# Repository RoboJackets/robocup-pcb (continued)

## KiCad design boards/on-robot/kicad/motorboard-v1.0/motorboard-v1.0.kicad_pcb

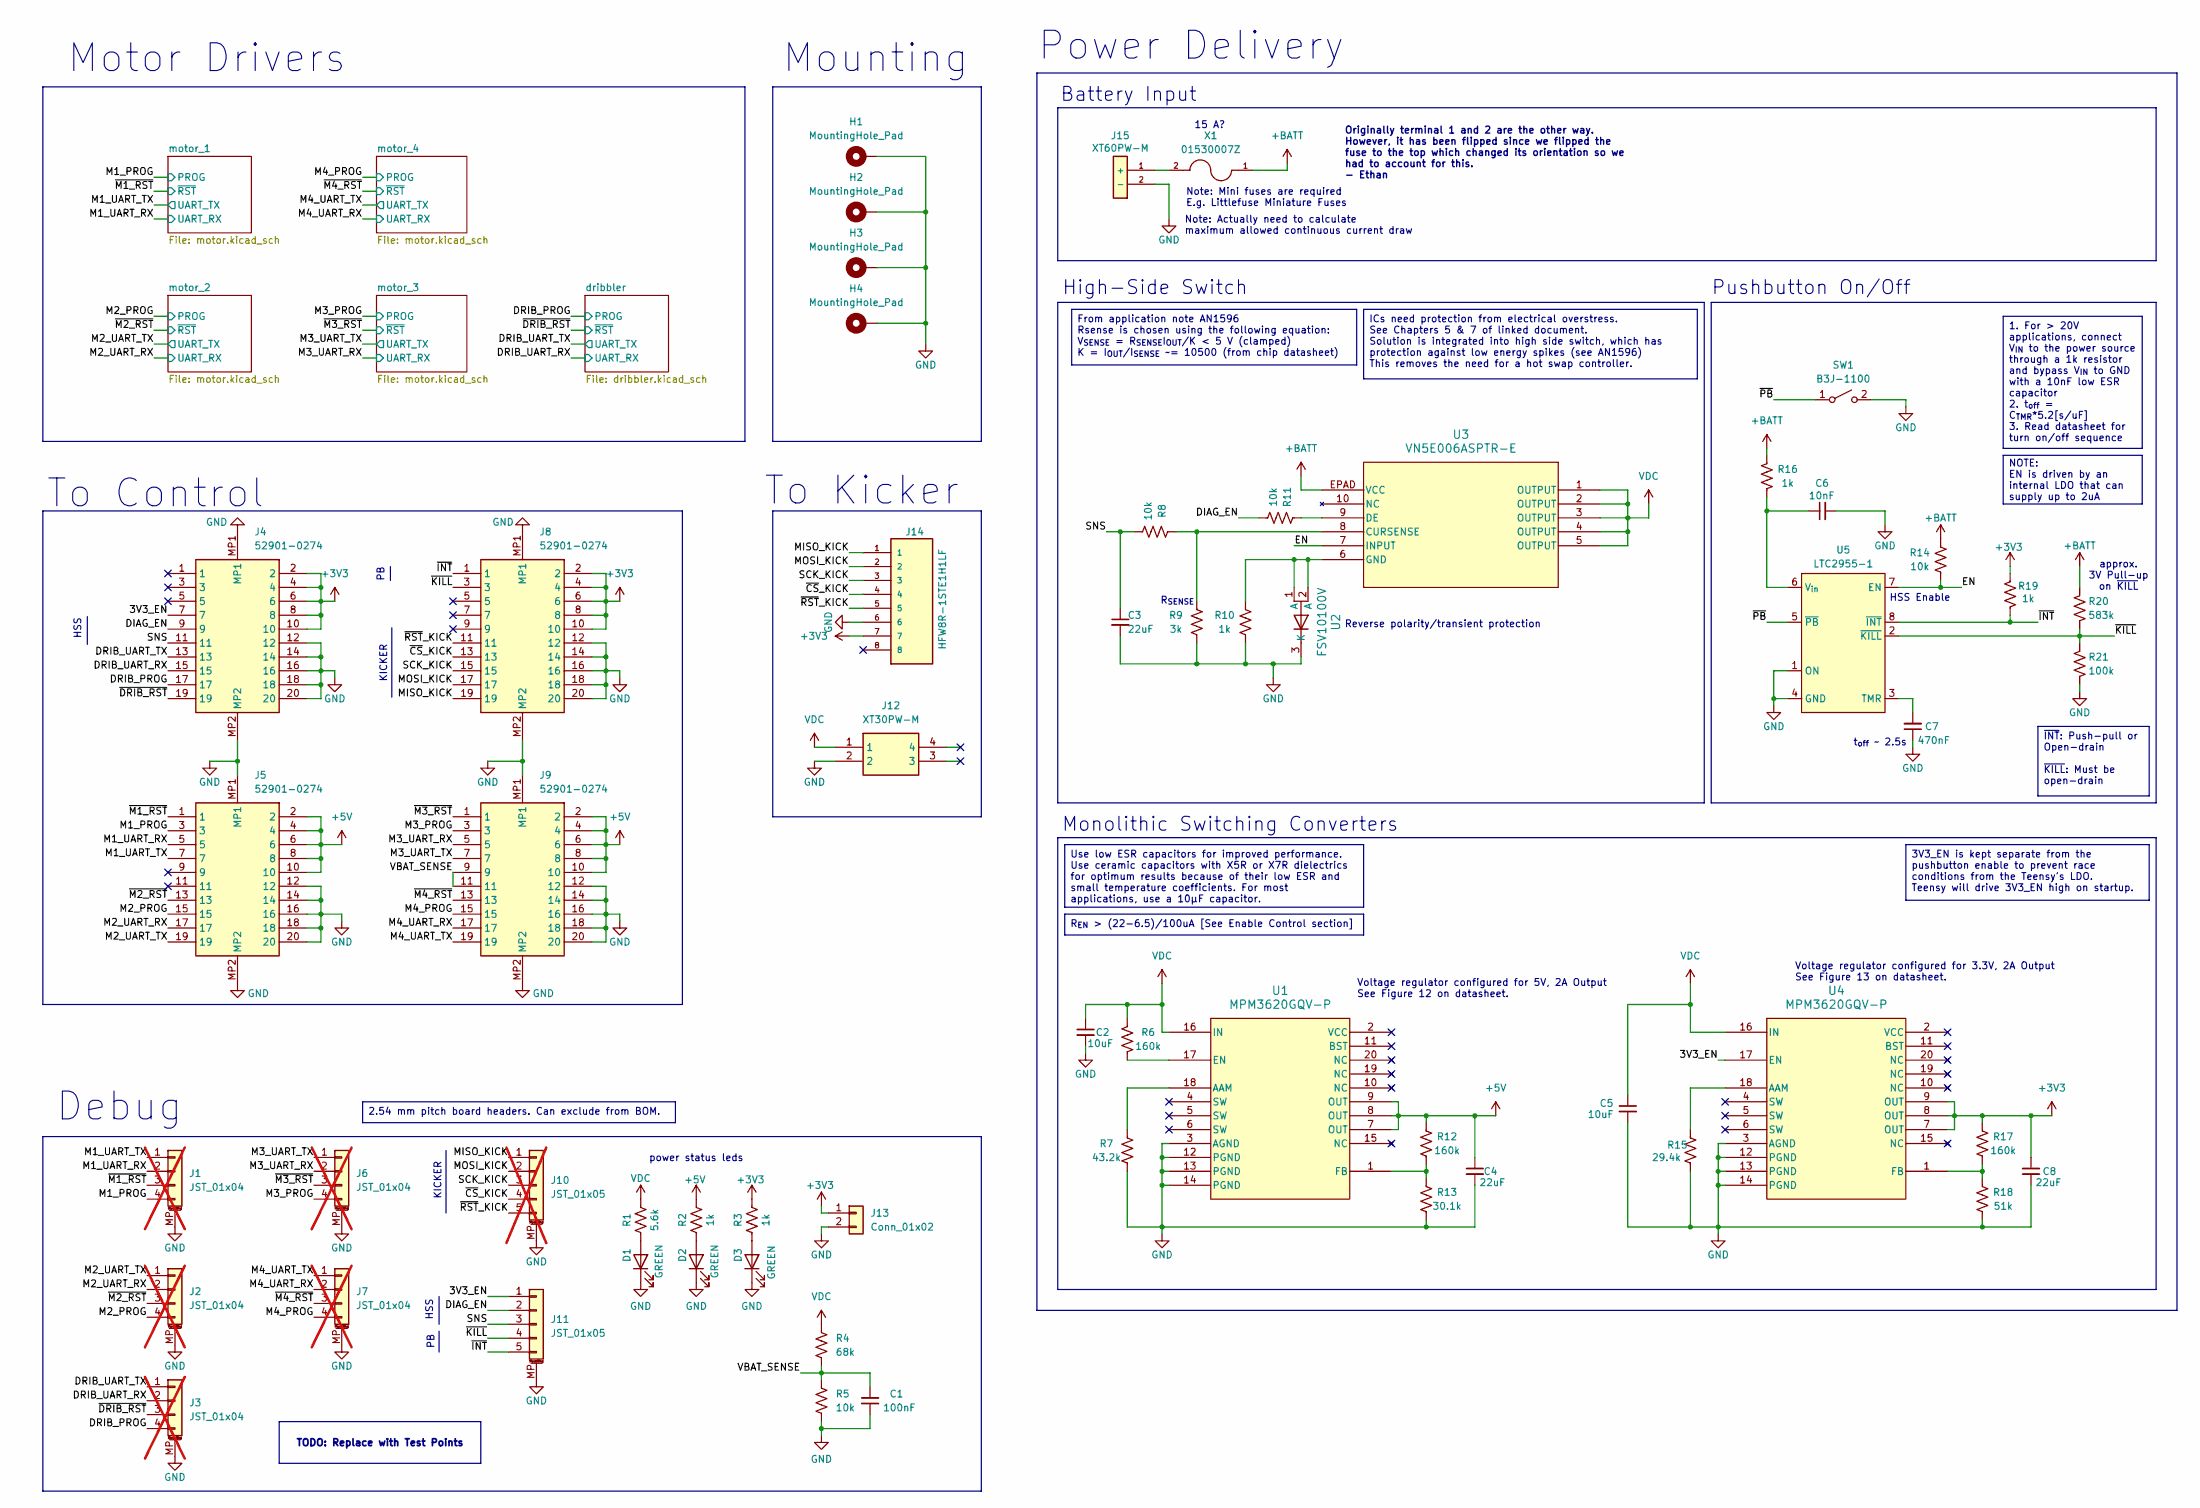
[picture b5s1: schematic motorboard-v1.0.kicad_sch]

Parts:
C1: 100nF; C_0603_1608Metric
C2, C5: 10uF; C_1206_3216Metric
C3, C4, C8: 22uF; C_1206_3216Metric
C6: 10nF; C_0603_1608Metric
C7: 470nF; C_0603_1608Metric
D1, D2, D3: GREEN; D_0603_1608Metric
H1, H2, H3, H4: MountingHole_Pad; MountingHole_3.7mm_Pad
J1, J2, J3, J6, J7: JST_01x04; JST_SH_BM04B-SRSS-TB_1x04-1MP_P1.00mm_Vertical; not fitted
J4, J5, J8, J9: 52901-0274; 529010274; Manufacturer_Part_Number 52901-0274; Mouser Part Number 538-52901-0274
J10: JST_01x05; JST_SH_BM05B-SRSS-TB_1x05-1MP_P1.00mm_Vertical; not fitted
J11: JST_01x05; JST_SH_BM05B-SRSS-TB_1x05-1MP_P1.00mm_Vertical
J12: XT30PW-M; XT30PWM; Manufacturer P/N XT30PW-M
J13: Conn_01x02; PinHeader_1x02_P2.54mm_Vertical
J14: HFW8R-1STE1H1LF; AMPHENOL_HFW8R-1STE1H1LF; PARTREV B
J15: XT60PW-M; XT60PWM; Manufacturer P/N XT60PW-M
R1: 5.6k; R_0603_1608Metric
R2, R3, R10, R16, R19: 1k; R_0603_1608Metric
R4: 68k; R_0603_1608Metric
R5, R8, R11, R14: 10k; R_0603_1608Metric
R6, R12, R17: 160k; R_0603_1608Metric
R7: 43.2k; R_0603_1608Metric
R9: 3k; R_0603_1608Metric
R13: 30.1k; R_0603_1608Metric
R15: 29.4k; R_0603_1608Metric
R18: 51k; R_0603_1608Metric
R20: 583k; R_0603_1608Metric
R21: 100k; R_0603_1608Metric
SW1: B3J-1100; B3J-1000
U1, U4: MPM3620GQV-P; MPM3620GQVP; Manufacturer P/N MPM3620GQV-P
U2: FSV10100V; DIO_10100V_ONS; Manufacturer P/N FSV10100V
U3: VN5E006ASPTR-E; SO_E006ASP-E_STM; Manufacturer P/N VN5E006ASPTR-E
U5: LTC2955-1; SOT65P280X100-8N; Manufacturer P/N LTC2955CTS8-1#TRMPBF
X1: 01530007Z; FUSE_01530007Z; Manufacturer P/N 01530007Z

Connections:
+3V3: C8.1, J4.2, J4.4, J4.6, J4.8, J4.10, J8.2, J8.4, J8.6, J8.8, J8.10, J13.1, J14.7, R3.2, R17.2, R19.2, U4.7 (OUT), U4.8 (OUT), U4.9 (OUT); also elsewhere on the board
+5V: C4.1, J5.2, J5.4, J5.6, J5.8, J5.10, J9.2, J9.4, J9.6, J9.8, J9.10, R2.2, R12.2, U1.7 (OUT), U1.8 (OUT), U1.9 (OUT); also elsewhere on the board
+BATT: R14.2, R16.2, R20.2, U3.EPAD (VCC), X1.1
/3V3_EN: J4.7, J11.1, U4.17 (EN)
/DIAG_EN: J4.9, J11.2, R11.1
/DRIB_PROG: J3.4, J4.17; also elsewhere on the board
/DRIB_UART_RX: J3.2, J4.15; also elsewhere on the board
/DRIB_UART_TX: J3.1, J4.13; also elsewhere on the board
/EN: R14.1, U3.7 (INPUT), U5.7 (EN)
/M1_PROG: J1.4, J5.3; also elsewhere on the board
/M1_UART_RX: J1.2, J5.5; also elsewhere on the board
/M1_UART_TX: J1.1, J5.7; also elsewhere on the board
/M2_PROG: J2.4, J5.15; also elsewhere on the board
/M2_UART_RX: J2.2, J5.17; also elsewhere on the board
/M2_UART_TX: J2.1, J5.19; also elsewhere on the board
/M3_PROG: J6.4, J9.3; also elsewhere on the board
/M3_UART_RX: J6.2, J9.5; also elsewhere on the board
/M3_UART_TX: J6.1, J9.7; also elsewhere on the board
/M4_PROG: J7.4, J9.15; also elsewhere on the board
/M4_UART_RX: J7.2, J9.17; also elsewhere on the board
/M4_UART_TX: J7.1, J9.19; also elsewhere on the board
/MISO_KICK: J8.19, J10.1, J14.1
/MOSI_KICK: J8.17, J10.2, J14.2
/SCK_KICK: J8.15, J10.3, J14.3
/SNS: C3.1, J4.11, J11.3, R8.1
/VBAT_SENSE: C1.2, J9.9, J9.11, R4.2, R5.1
/~CS_KICK: J8.13, J10.4, J14.4
/~DRIB_RST: J3.3, J4.19; also elsewhere on the board
/~INT: J8.1, J11.5, R19.1, U5.8 (~INT)
/~KILL: J8.3, J11.4, R20.1, R21.2, U5.2 (~KILL)
/~M1_RST: J1.3, J5.1; also elsewhere on the board
/~M2_RST: J2.3, J5.13; also elsewhere on the board
/~M3_RST: J6.3, J9.1; also elsewhere on the board
/~M4_RST: J7.3, J9.13; also elsewhere on the board
/~PB: SW1.1 (A), U5.5 (~PB)
/~RST_KICK: J8.11, J10.5, J14.5
GND: C1.1, C2.2, C3.2, C4.2, C5.2, C6.2, C7.1, C8.2, D1.1 (K), D2.1 (K), D3.1 (K), H1.1 (1_1), H2.1 (1_1), H3.1 (1_1), H4.1 (1_1), J1.MP (MountPin), J2.MP (MountPin), J3.MP (MountPin), J4.12, J4.14, J4.16, J4.18, J4.20, J4.MP1, J4.MP2, J5.12, J5.14, J5.16, J5.18, J5.20, J5.MP1, J5.MP2, J6.MP (MountPin), J7.MP (MountPin), J8.12, J8.14, J8.16, J8.18, J8.20, J8.MP1, J8.MP2, J9.12, J9.14, J9.16, J9.18, J9.20, J9.MP1, J9.MP2, J10.MP (MountPin), J11.MP (MountPin), J12.2, J13.2, J14.6, J15.2 (-), R5.2, R7.1, R9.1, R10.1, R13.1, R15.1, R18.1, R21.1, SW1.2 (B), U1.3 (AGND), U1.12 (PGND), U1.13 (PGND), U1.14 (PGND), U2.3 (K), U4.3 (AGND), U4.12 (PGND), U4.13 (PGND), U4.14 (PGND), U5.1 (ON), U5.4 (GND); also elsewhere on the board
unnamed: D1.2 (A), R1.1
unnamed: D2.2 (A), R2.1
unnamed: D3.2 (A), R3.1
unnamed: J15.1 (+), X1.2
unnamed: R7.2, U1.18 (AAM)
unnamed: R6.1, U1.17 (EN)
unnamed: R12.1, R13.2, U1.1 (FB)
unnamed: R8.2, R9.2, U3.8 (CURSENSE)
unnamed: R11.2, U3.9 (DE)
unnamed: R10.2, U2.1 (A), U2.2 (A), U3.6 (GND)
unnamed: R15.2, U4.18 (AAM)
unnamed: R17.1, R18.2, U4.1 (FB)
unnamed: C7.2, U5.3 (TMR)
unnamed: C6.1, R16.1, U5.6 (V_{in})
VDC: C2.1, C5.1, J12.1, R1.2, R4.1, R6.2, U1.16 (IN), U3.1 (OUTPUT), U3.2 (OUTPUT), U3.3 (OUTPUT), U3.4 (OUTPUT), U3.5 (OUTPUT), U4.16 (IN); also elsewhere on the board

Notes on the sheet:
Mounting
HSS
Reverse polarity/transient protection
Debug
KICKER
Battery Input
Voltage regulator configured for 3.3V, 2A Output See Figure 13 on datasheet.
Originally terminal 1 and 2 are the other way. However, it has been flipped since we flipped the fuse to the top which changed its orientation so we had to account for this. - Ethan
HSS Enable
Power Delivery
power status leds
15 A?
Note: Mini fuses are required E.g. Littlefuse Miniature Fuses
To Kicker
Monolithic Switching Converters
High-Side Switch
R_{SENSE}
Note: Actually need to calculate maximum allowed continuous current draw
Voltage regulator configured for 5V, 2A Output See Figure 12 on datasheet.
approx. 3V Pull-up on ~{KILL}
Pushbutton On/Off
Motor Drivers
To Control
t_{off} ~ 2.5s
~{INT}: Push-pull or Open-drain ~{KILL}: Must be open-drain
R_{EN} > (22-6.5)/100uA [See Enable Control section]
1. For > 20V applications, connect V_{IN} to the power source through a 1k resistor and bypass V_{IN} to GND with a 10nF low ESR capacitor 2. t_{off} = C_{TMR}*5.2[s/uF] 3. Read datasheet for turn on/off sequence
TODO: Replace with Test Points
From application note AN1596 Rsense is chosen using the following equation: V_{SENSE} = R_{SENSE}I_{OUT}/K < 5 V (clamped) K = I_{OUT}/I_{SENSE} ~= 10500 (from chip datasheet)
NOTE: EN is driven by an internal LDO that can supply up to 2uA
Use low ESR capacitors for improved performance. Use ceramic capacitors with X5R or X7R dielectrics for optimum results because of their low ESR and small temperature coefficients. For most applications, use a 10μF capacitor.
3V3_EN is kept separate from the pushbutton enable to prevent race conditions from the Teensy's LDO. Teensy will drive 3V3_EN high on startup.
ICs need protection from electrical overstress. See Chapters 5 & 7 of linked document. Solution is integrated into high side switch, which has protection against low energy spikes (see AN1596) This removes the need for a hot swap controller.
2.54 mm pitch board headers. Can exclude from BOM.

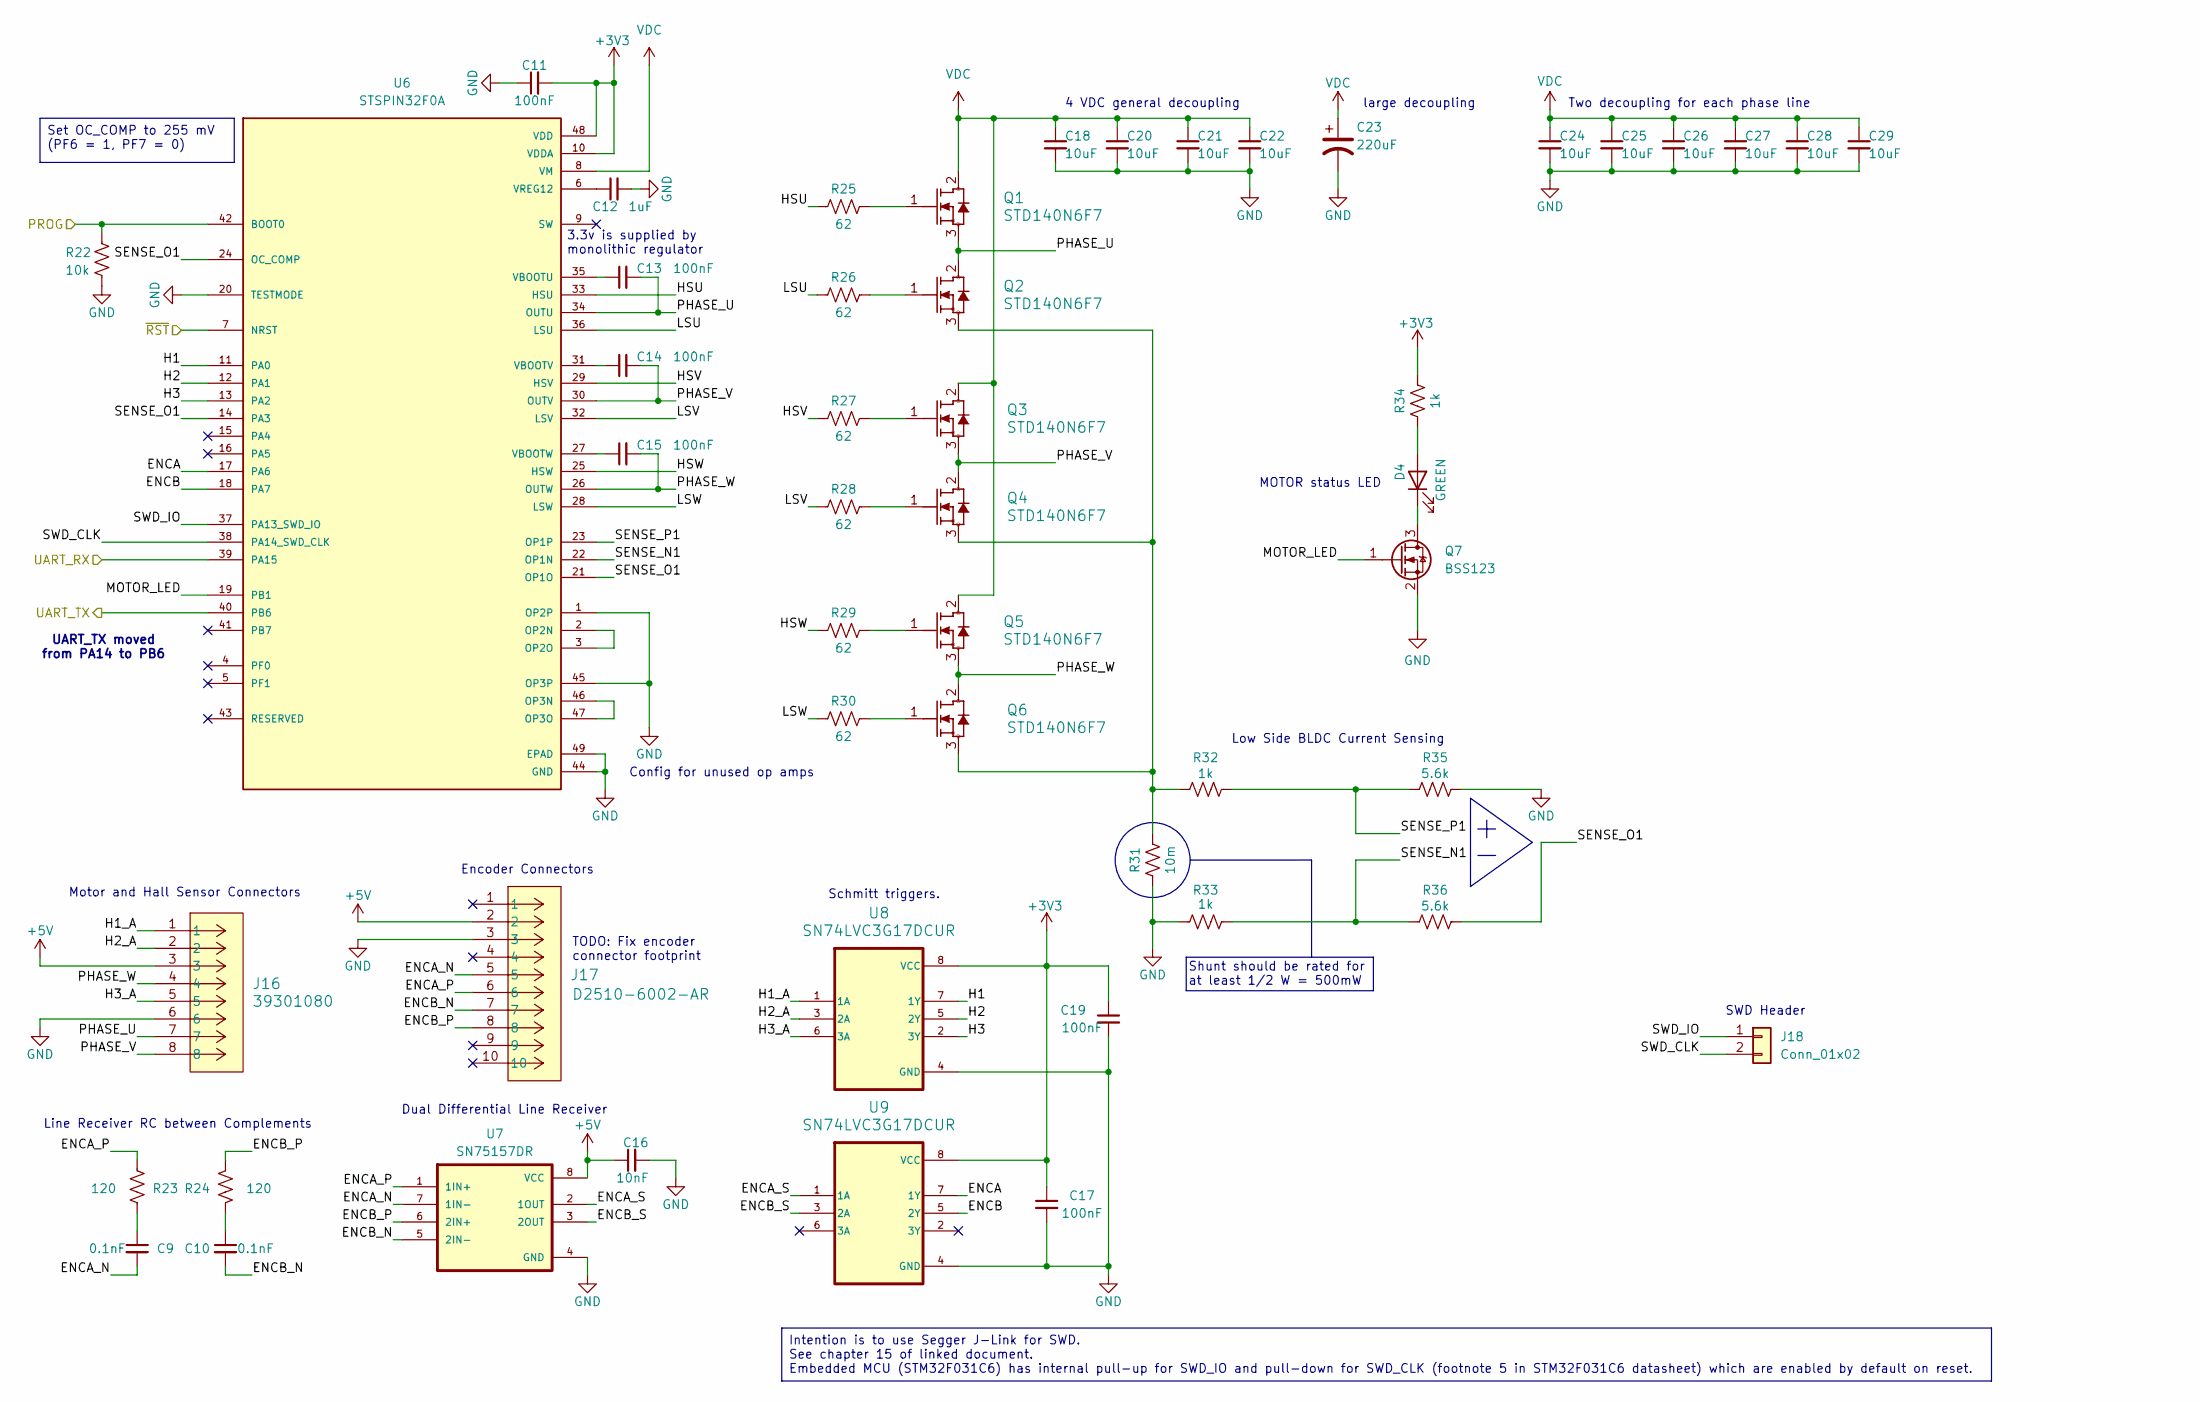
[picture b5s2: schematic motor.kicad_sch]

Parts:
C9, C10: 0.1nF; C_0603_1608Metric
C11, C13, C14, C15, C17, C19: 100nF; C_0603_1608Metric
C12: 1uF; C_0603_1608Metric
C16: 10nF; C_1206_3216Metric
C18, C20, C21, C22, C24, C25, C26, C27, C28, C29: 10uF; C_1206_3216Metric
C23: 220uF; CP_Elec_6.3x7.7
D4: GREEN; D_0603_1608Metric
J16: 39301080; Molex_Mini-Fit_Jr_5566-08A_2x04_P4.20mm_Vertical; Manufacturer P/N 0039301080
J17: D2510-6002-AR; CONN_6002RB_3MM; Manufacturer P/N MHC10E-ND
J18: Conn_01x02; PinHeader_1x02_P2.54mm_Vertical
Q1, Q2, Q3, Q4, Q5, Q6: STD140N6F7; DPAKTO-252_A2_STM; Manufacturer P/N STD140N6F7
Q7: BSS123; SOT-23
R22: 10k; R_0603_1608Metric
R23, R24: 120; R_0603_1608Metric
R25, R26, R27, R28, R29, R30: 62; R_0603_1608Metric
R31: 10m; R_1206_3216Metric
R32, R33, R34: 1k; R_0603_1608Metric
R35, R36: 5.6k; R_0603_1608Metric
U6: STSPIN32F0A; IC_STSPIN32F0A; Manufacturer P/N STSPIN32F0A
U7: SN75157DR; SOIC127P599X175-8N
U8, U9: SN74LVC3G17DCUR; SOP50P310X90-8N; Manufacturer P/N SN74LVC3G17DCTR

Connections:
+3V3: C11.2, C17.1, C19.1, R34.2, U6.10 (VDDA), U6.48 (VDD), U8.8 (VCC), U9.8 (VCC); also elsewhere on the board
+5V: C16.1, J16.3, J17.2, U7.8 (VCC); also elsewhere on the board
/M1_PROG: R22.1, U6.42 (BOOT0); also elsewhere on the board
/M1_UART_RX: U6.39 (PA15); also elsewhere on the board
/M1_UART_TX: U6.40 (PB6); also elsewhere on the board
/motor_1/ENCA: U6.17 (PA6), U9.7 (1Y)
/motor_1/ENCA_N: C9.2, J17.5, U7.7 (1IN-)
/motor_1/ENCA_P: J17.6, R23.2, U7.1 (1IN+)
/motor_1/ENCA_S: U7.2 (1OUT), U9.1 (1A)
/motor_1/ENCB: U6.18 (PA7), U9.5 (2Y)
/motor_1/ENCB_N: C10.2, J17.7, U7.5 (2IN-)
/motor_1/ENCB_P: J17.8, R24.2, U7.6 (2IN+)
/motor_1/ENCB_S: U7.3 (2OUT), U9.3 (2A)
/motor_1/H1: U6.11 (PA0), U8.7 (1Y)
/motor_1/H1_A: J16.1, U8.1 (1A)
/motor_1/H2: U6.12 (PA1), U8.5 (2Y)
/motor_1/H2_A: J16.2, U8.3 (2A)
/motor_1/H3: U6.13 (PA2), U8.2 (3Y)
/motor_1/H3_A: J16.5, U8.6 (3A)
/motor_1/HSU: R25.1, U6.33 (HSU)
/motor_1/HSV: R27.1, U6.29 (HSV)
/motor_1/HSW: R29.1, U6.25 (HSW)
/motor_1/LSU: R26.1, U6.36 (LSU)
/motor_1/LSV: R28.1, U6.32 (LSV)
/motor_1/LSW: R30.1, U6.28 (LSW)
/motor_1/MOTOR_LED: Q7.1 (G), U6.19 (PB1)
/motor_1/PHASE_U: C13.2, J16.7, Q1.3 (S), Q2.2 (D), U6.34 (OUTU)
/motor_1/PHASE_V: C14.2, J16.8, Q3.3 (S), Q4.2 (D), U6.30 (OUTV)
/motor_1/PHASE_W: C15.2, J16.4, Q5.3 (S), Q6.2 (D), U6.26 (OUTW)
/motor_1/SENSE_N1: R33.2, R36.1, U6.22 (OP1N)
/motor_1/SENSE_O1: R36.2, U6.14 (PA3), U6.21 (OP1O), U6.24 (OC_COMP)
/motor_1/SENSE_P1: R32.2, R35.1, U6.23 (OP1P)
/motor_1/SWD_CLK: J18.2, U6.38 (PA14_SWD_CLK)
/motor_1/SWD_IO: J18.1, U6.37 (PA13_SWD_IO)
/~M1_RST: U6.7 (NRST); also elsewhere on the board
GND: C11.1, C12.2, C16.2, C17.2, C18.2, C19.2, C20.2, C21.2, C22.2, C23.2, C24.2, C25.2, C26.2, C27.2, C28.2, C29.2, J16.6, J17.3, Q7.2 (S), R22.2, R31.1, R33.1, R35.2, U6.1 (OP2P), U6.20 (TESTMODE), U6.44 (GND), U6.45 (OP3P), U6.49 (EPAD), U7.4 (GND), U8.4 (GND), U9.4 (GND); also elsewhere on the board
unnamed: C9.1, R23.1
unnamed: C10.1, R24.1
unnamed: D4.2 (A), R34.1
unnamed: D4.1 (K), Q7.3 (D)
unnamed: Q1.1 (G), R25.2
unnamed: Q2.1 (G), R26.2
unnamed: Q2.3 (S), Q4.3 (S), Q6.3 (S), R31.2, R32.1
unnamed: Q3.1 (G), R27.2
unnamed: Q4.1 (G), R28.2
unnamed: Q5.1 (G), R29.2
unnamed: Q6.1 (G), R30.2
unnamed: U6.2 (OP2N), U6.3 (OP2O)
unnamed: U6.46 (OP3N), U6.47 (OP3O)
unnamed: C13.1, U6.35 (VBOOTU)
unnamed: C14.1, U6.31 (VBOOTV)
unnamed: C15.1, U6.27 (VBOOTW)
unnamed: C12.1, U6.6 (VREG12)
VDC: C18.1, C20.1, C21.1, C22.1, C23.1, C24.1, C25.1, C26.1, C27.1, C28.1, C29.1, Q1.2 (D), Q3.2 (D), Q5.2 (D), U6.8 (VM); also elsewhere on the board

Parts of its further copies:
C30, C31, C51, C52, C72, C73: 0.1nF; C_0603_1608Metric
C32, C34, C35, C36, C38, C40, C53, C55, C56, C57, C59, C61, C74, C76, C77, C78, C80, C82: 100nF; C_0603_1608Metric
C33, C54, C75: 1uF; C_0603_1608Metric
C37, C58, C79: 10nF; C_1206_3216Metric
C39, C41, C42, C43, C45, C46, C47, C48, C49, C50, C60, C62, C63, C64, C66, C67, C68, C69, C70, C71, C81, C83, C84, C85, C87, C88, C89, C90, C91, C92: 10uF; C_1206_3216Metric
C44, C65, C86: 220uF; CP_Elec_6.3x7.7
D5, D6, D7: GREEN; D_0603_1608Metric
J19, J22, J25: 39301080; Molex_Mini-Fit_Jr_5566-08A_2x04_P4.20mm_Vertical; Manufacturer P/N 0039301080
J20, J23, J26: D2510-6002-AR; CONN_6002RB_3MM; Manufacturer P/N MHC10E-ND
J21, J24, J27: Conn_01x02; PinHeader_1x02_P2.54mm_Vertical
Q8, Q9, Q10, Q11, Q12, Q13, Q15, Q16, Q17, Q18, Q19, Q20, Q22, Q23, Q24, Q25, Q26, Q27: STD140N6F7; DPAKTO-252_A2_STM; Manufacturer P/N STD140N6F7
Q14, Q21, Q28: BSS123; SOT-23
R37, R52, R67: 10k; R_0603_1608Metric
R38, R39, R53, R54, R68, R69: 120; R_0603_1608Metric
R40, R41, R42, R43, R44, R45, R55, R56, R57, R58, R59, R60, R70, R71, R72, R73, R74, R75: 62; R_0603_1608Metric
R46, R61, R76: 10m; R_1206_3216Metric
R47, R48, R49, R62, R63, R64, R77, R78, R79: 1k; R_0603_1608Metric
R50, R51, R65, R66, R80, R81: 5.6k; R_0603_1608Metric
U10, U14, U18: STSPIN32F0A; IC_STSPIN32F0A; Manufacturer P/N STSPIN32F0A
U11, U15, U19: SN75157DR; SOIC127P599X175-8N
U12, U13, U16, U17, U20, U21: SN74LVC3G17DCUR; SOP50P310X90-8N; Manufacturer P/N SN74LVC3G17DCTR

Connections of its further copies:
+3V3: C32.2, C38.1, C40.1, C53.2, C59.1, C61.1, C74.2, C80.1, C82.1, R49.2, R64.2, R79.2, U10.10 (VDDA), U10.48 (VDD), U12.8 (VCC), U13.8 (VCC), U14.10 (VDDA), U14.48 (VDD), U16.8 (VCC), U17.8 (VCC), U18.10 (VDDA), U18.48 (VDD), U20.8 (VCC), U21.8 (VCC); also elsewhere on the board
+5V: C37.1, C58.1, C79.1, J19.3, J20.2, J22.3, J23.2, J25.3, J26.2, U11.8 (VCC), U15.8 (VCC), U19.8 (VCC); also elsewhere on the board
/M2_PROG: R37.1, U10.42 (BOOT0); also elsewhere on the board
/M2_UART_RX: U10.39 (PA15); also elsewhere on the board
/M2_UART_TX: U10.40 (PB6); also elsewhere on the board
/M3_PROG: R52.1, U14.42 (BOOT0); also elsewhere on the board
/M3_UART_RX: U14.39 (PA15); also elsewhere on the board
/M3_UART_TX: U14.40 (PB6); also elsewhere on the board
/M4_PROG: R67.1, U18.42 (BOOT0); also elsewhere on the board
/M4_UART_RX: U18.39 (PA15); also elsewhere on the board
/M4_UART_TX: U18.40 (PB6); also elsewhere on the board
/motor_2/ENCA: U10.17 (PA6), U13.7 (1Y)
/motor_2/ENCA_N: C30.2, J20.5, U11.7 (1IN-)
/motor_2/ENCA_P: J20.6, R38.2, U11.1 (1IN+)
/motor_2/ENCA_S: U11.2 (1OUT), U13.1 (1A)
/motor_2/ENCB: U10.18 (PA7), U13.5 (2Y)
/motor_2/ENCB_N: C31.2, J20.7, U11.5 (2IN-)
/motor_2/ENCB_P: J20.8, R39.2, U11.6 (2IN+)
/motor_2/ENCB_S: U11.3 (2OUT), U13.3 (2A)
/motor_2/H1: U10.11 (PA0), U12.7 (1Y)
/motor_2/H1_A: J19.1, U12.1 (1A)
/motor_2/H2: U10.12 (PA1), U12.5 (2Y)
/motor_2/H2_A: J19.2, U12.3 (2A)
/motor_2/H3: U10.13 (PA2), U12.2 (3Y)
/motor_2/H3_A: J19.5, U12.6 (3A)
/motor_2/HSU: R40.1, U10.33 (HSU)
/motor_2/HSV: R42.1, U10.29 (HSV)
/motor_2/HSW: R44.1, U10.25 (HSW)
/motor_2/LSU: R41.1, U10.36 (LSU)
/motor_2/LSV: R43.1, U10.32 (LSV)
/motor_2/LSW: R45.1, U10.28 (LSW)
/motor_2/MOTOR_LED: Q14.1 (G), U10.19 (PB1)
/motor_2/PHASE_U: C34.2, J19.7, Q8.3 (S), Q9.2 (D), U10.34 (OUTU)
/motor_2/PHASE_V: C35.2, J19.8, Q10.3 (S), Q11.2 (D), U10.30 (OUTV)
/motor_2/PHASE_W: C36.2, J19.4, Q12.3 (S), Q13.2 (D), U10.26 (OUTW)
/motor_2/SENSE_N1: R48.2, R51.1, U10.22 (OP1N)
/motor_2/SENSE_O1: R51.2, U10.14 (PA3), U10.21 (OP1O), U10.24 (OC_COMP)
/motor_2/SENSE_P1: R47.2, R50.1, U10.23 (OP1P)
/motor_2/SWD_CLK: J21.2, U10.38 (PA14_SWD_CLK)
/motor_2/SWD_IO: J21.1, U10.37 (PA13_SWD_IO)
/motor_3/ENCA: U14.17 (PA6), U17.7 (1Y)
/motor_3/ENCA_N: C51.2, J23.5, U15.7 (1IN-)
/motor_3/ENCA_P: J23.6, R53.2, U15.1 (1IN+)
/motor_3/ENCA_S: U15.2 (1OUT), U17.1 (1A)
/motor_3/ENCB: U14.18 (PA7), U17.5 (2Y)
/motor_3/ENCB_N: C52.2, J23.7, U15.5 (2IN-)
/motor_3/ENCB_P: J23.8, R54.2, U15.6 (2IN+)
/motor_3/ENCB_S: U15.3 (2OUT), U17.3 (2A)
/motor_3/H1: U14.11 (PA0), U16.7 (1Y)
/motor_3/H1_A: J22.1, U16.1 (1A)
/motor_3/H2: U14.12 (PA1), U16.5 (2Y)
/motor_3/H2_A: J22.2, U16.3 (2A)
/motor_3/H3: U14.13 (PA2), U16.2 (3Y)
/motor_3/H3_A: J22.5, U16.6 (3A)
/motor_3/HSU: R55.1, U14.33 (HSU)
/motor_3/HSV: R57.1, U14.29 (HSV)
/motor_3/HSW: R59.1, U14.25 (HSW)
/motor_3/LSU: R56.1, U14.36 (LSU)
/motor_3/LSV: R58.1, U14.32 (LSV)
/motor_3/LSW: R60.1, U14.28 (LSW)
/motor_3/MOTOR_LED: Q21.1 (G), U14.19 (PB1)
/motor_3/PHASE_U: C55.2, J22.7, Q15.3 (S), Q16.2 (D), U14.34 (OUTU)
/motor_3/PHASE_V: C56.2, J22.8, Q17.3 (S), Q18.2 (D), U14.30 (OUTV)
/motor_3/PHASE_W: C57.2, J22.4, Q19.3 (S), Q20.2 (D), U14.26 (OUTW)
/motor_3/SENSE_N1: R63.2, R66.1, U14.22 (OP1N)
/motor_3/SENSE_O1: R66.2, U14.14 (PA3), U14.21 (OP1O), U14.24 (OC_COMP)
/motor_3/SENSE_P1: R62.2, R65.1, U14.23 (OP1P)
/motor_3/SWD_CLK: J24.2, U14.38 (PA14_SWD_CLK)
/motor_3/SWD_IO: J24.1, U14.37 (PA13_SWD_IO)
/motor_4/ENCA: U18.17 (PA6), U21.7 (1Y)
/motor_4/ENCA_N: C72.2, J26.5, U19.7 (1IN-)
/motor_4/ENCA_P: J26.6, R68.2, U19.1 (1IN+)
/motor_4/ENCA_S: U19.2 (1OUT), U21.1 (1A)
/motor_4/ENCB: U18.18 (PA7), U21.5 (2Y)
/motor_4/ENCB_N: C73.2, J26.7, U19.5 (2IN-)
/motor_4/ENCB_P: J26.8, R69.2, U19.6 (2IN+)
/motor_4/ENCB_S: U19.3 (2OUT), U21.3 (2A)
/motor_4/H1: U18.11 (PA0), U20.7 (1Y)
/motor_4/H1_A: J25.1, U20.1 (1A)
/motor_4/H2: U18.12 (PA1), U20.5 (2Y)
/motor_4/H2_A: J25.2, U20.3 (2A)
/motor_4/H3: U18.13 (PA2), U20.2 (3Y)
/motor_4/H3_A: J25.5, U20.6 (3A)
/motor_4/HSU: R70.1, U18.33 (HSU)
/motor_4/HSV: R72.1, U18.29 (HSV)
/motor_4/HSW: R74.1, U18.25 (HSW)
/motor_4/LSU: R71.1, U18.36 (LSU)
/motor_4/LSV: R73.1, U18.32 (LSV)
/motor_4/LSW: R75.1, U18.28 (LSW)
/motor_4/MOTOR_LED: Q28.1 (G), U18.19 (PB1)
/motor_4/PHASE_U: C76.2, J25.7, Q22.3 (S), Q23.2 (D), U18.34 (OUTU)
/motor_4/PHASE_V: C77.2, J25.8, Q24.3 (S), Q25.2 (D), U18.30 (OUTV)
/motor_4/PHASE_W: C78.2, J25.4, Q26.3 (S), Q27.2 (D), U18.26 (OUTW)
/motor_4/SENSE_N1: R78.2, R81.1, U18.22 (OP1N)
/motor_4/SENSE_O1: R81.2, U18.14 (PA3), U18.21 (OP1O), U18.24 (OC_COMP)
/motor_4/SENSE_P1: R77.2, R80.1, U18.23 (OP1P)
/motor_4/SWD_CLK: J27.2, U18.38 (PA14_SWD_CLK)
/motor_4/SWD_IO: J27.1, U18.37 (PA13_SWD_IO)
/~M2_RST: U10.7 (NRST); also elsewhere on the board
/~M3_RST: U14.7 (NRST); also elsewhere on the board
/~M4_RST: U18.7 (NRST); also elsewhere on the board
GND: C32.1, C33.2, C37.2, C38.2, C39.2, C40.2, C41.2, C42.2, C43.2, C44.2, C45.2, C46.2, C47.2, C48.2, C49.2, C50.2, C53.1, C54.2, C58.2, C59.2, C60.2, C61.2, C62.2, C63.2, C64.2, C65.2, C66.2, C67.2, C68.2, C69.2, C70.2, C71.2, C74.1, C75.2, C79.2, C80.2, C81.2, C82.2, C83.2, C84.2, C85.2, C86.2, C87.2, C88.2, C89.2, C90.2, C91.2, C92.2, J19.6, J20.3, J22.6, J23.3, J25.6, J26.3, Q14.2 (S), Q21.2 (S), Q28.2 (S), R37.2, R46.1, R48.1, R50.2, R52.2, R61.1, R63.1, R65.2, R67.2, R76.1, R78.1, R80.2, U10.1 (OP2P), U10.20 (TESTMODE), U10.44 (GND), U10.45 (OP3P), U10.49 (EPAD), U11.4 (GND), U12.4 (GND), U13.4 (GND), U14.1 (OP2P), U14.20 (TESTMODE), U14.44 (GND), U14.45 (OP3P), U14.49 (EPAD), U15.4 (GND), U16.4 (GND), U17.4 (GND), U18.1 (OP2P), U18.20 (TESTMODE), U18.44 (GND), U18.45 (OP3P), U18.49 (EPAD), U19.4 (GND), U20.4 (GND), U21.4 (GND); also elsewhere on the board
unnamed: C30.1, R38.1
unnamed: C31.1, R39.1
unnamed: C51.1, R53.1
unnamed: C52.1, R54.1
unnamed: C72.1, R68.1
unnamed: C73.1, R69.1
unnamed: D5.2 (A), R49.1
unnamed: D5.1 (K), Q14.3 (D)
unnamed: D6.2 (A), R64.1
unnamed: D6.1 (K), Q21.3 (D)
unnamed: D7.2 (A), R79.1
unnamed: D7.1 (K), Q28.3 (D)
unnamed: Q8.1 (G), R40.2
unnamed: Q9.1 (G), R41.2
unnamed: Q10.1 (G), R42.2
unnamed: Q11.1 (G), R43.2
unnamed: Q9.3 (S), Q11.3 (S), Q13.3 (S), R46.2, R47.1
unnamed: Q12.1 (G), R44.2
unnamed: Q13.1 (G), R45.2
unnamed: Q15.1 (G), R55.2
unnamed: Q16.1 (G), R56.2
unnamed: Q16.3 (S), Q18.3 (S), Q20.3 (S), R61.2, R62.1
unnamed: Q17.1 (G), R57.2
unnamed: Q18.1 (G), R58.2
unnamed: Q19.1 (G), R59.2
unnamed: Q20.1 (G), R60.2
unnamed: Q22.1 (G), R70.2
unnamed: Q23.1 (G), R71.2
unnamed: Q23.3 (S), Q25.3 (S), Q27.3 (S), R76.2, R77.1
unnamed: Q24.1 (G), R72.2
unnamed: Q25.1 (G), R73.2
unnamed: Q26.1 (G), R74.2
unnamed: Q27.1 (G), R75.2
unnamed: U10.2 (OP2N), U10.3 (OP2O)
unnamed: U10.46 (OP3N), U10.47 (OP3O)
unnamed: C34.1, U10.35 (VBOOTU)
unnamed: C35.1, U10.31 (VBOOTV)
unnamed: C36.1, U10.27 (VBOOTW)
unnamed: C33.1, U10.6 (VREG12)
unnamed: U14.2 (OP2N), U14.3 (OP2O)
unnamed: U14.46 (OP3N), U14.47 (OP3O)
unnamed: C55.1, U14.35 (VBOOTU)
unnamed: C56.1, U14.31 (VBOOTV)
unnamed: C57.1, U14.27 (VBOOTW)
unnamed: C54.1, U14.6 (VREG12)
unnamed: U18.2 (OP2N), U18.3 (OP2O)
unnamed: U18.46 (OP3N), U18.47 (OP3O)
unnamed: C76.1, U18.35 (VBOOTU)
unnamed: C77.1, U18.31 (VBOOTV)
unnamed: C78.1, U18.27 (VBOOTW)
unnamed: C75.1, U18.6 (VREG12)
VDC: C39.1, C41.1, C42.1, C43.1, C44.1, C45.1, C46.1, C47.1, C48.1, C49.1, C50.1, C60.1, C62.1, C63.1, C64.1, C65.1, C66.1, C67.1, C68.1, C69.1, C70.1, C71.1, C81.1, C83.1, C84.1, C85.1, C86.1, C87.1, C88.1, C89.1, C90.1, C91.1, C92.1, Q8.2 (D), Q10.2 (D), Q12.2 (D), Q15.2 (D), Q17.2 (D), Q19.2 (D), Q22.2 (D), Q24.2 (D), Q26.2 (D), U10.8 (VM), U14.8 (VM), U18.8 (VM); also elsewhere on the board

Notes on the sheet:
large decoupling
Shunt should be rated for at least 1/2 W = 500mW
Dual Differential Line Receiver
Config for unused op amps
Encoder Connectors
UART_TX moved from PA14 to PB6
Line Receiver RC between Complements
Motor and Hall Sensor Connectors
Schmitt triggers.
MOTOR status LED
TODO: Fix encoder connector footprint
3.3v is supplied by monolithic regulator
Two decoupling for each phase line
SWD Header
4 VDC general decoupling
Low Side BLDC Current Sensing
Set OC_COMP to 255 mV (PF6 = 1, PF7 = 0)
Intention is to use Segger J-Link for SWD. See chapter 15 of linked document. Embedded MCU (STM32F031C6) has internal pull-up for SWD_IO and pull-down for SWD_CLK (footnote 5 in STM32F031C6 datasheet) which are enabled by default on reset.

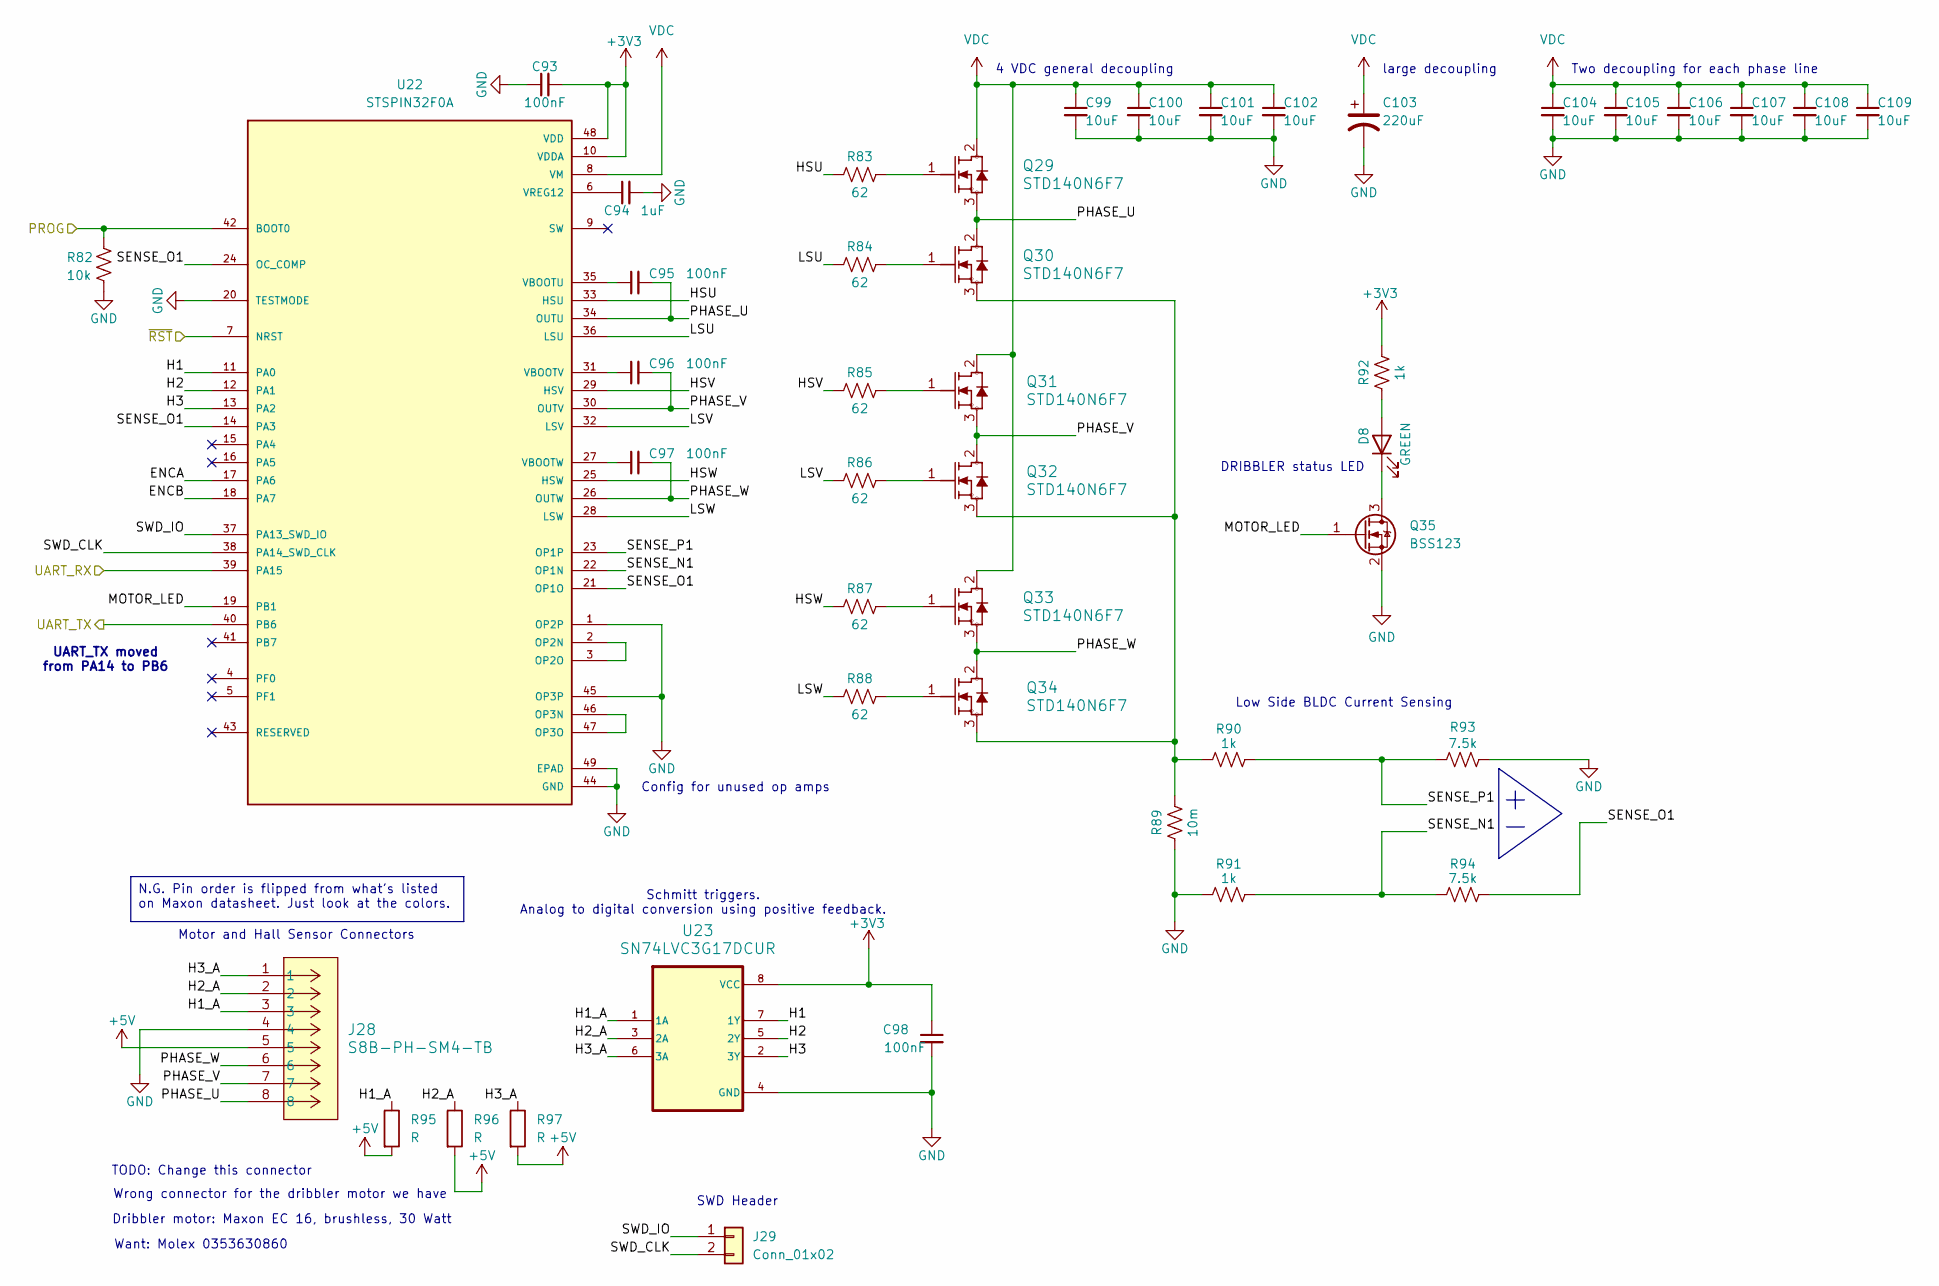
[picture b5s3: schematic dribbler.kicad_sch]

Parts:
C93, C95, C96, C97, C98: 100nF; C_0603_1608Metric
C94: 1uF; C_0603_1608Metric
C99, C100, C101, C102, C104, C105, C106, C107, C108, C109: 10uF; C_1206_3216Metric
C103: 220uF; CP_Elec_6.3x7.7
D8: GREEN; D_0603_1608Metric
J28: S8B-PH-SM4-TB; CONN_S8B-PH-SM4-TB_JST; Manufacturer P/N S8B-PH-SM4-TB
J29: Conn_01x02; PinHeader_1x02_P2.54mm_Vertical
Q29, Q30, Q31, Q32, Q33, Q34: STD140N6F7; DPAKTO-252_A2_STM; Manufacturer P/N STD140N6F7
Q35: BSS123; SOT-23
R82: 10k; R_0603_1608Metric
R83, R84, R85, R86, R87, R88: 62; R_0603_1608Metric
R89: 10m; R_1206_3216Metric
R90, R91, R92: 1k; R_0603_1608Metric
R93, R94: 7.5k; R_0603_1608Metric
R95, R96, R97: R; R_0603_1608Metric
U22: STSPIN32F0A; IC_STSPIN32F0A; Manufacturer P/N STSPIN32F0A
U23: SN74LVC3G17DCUR; SOP50P310X90-8N; Manufacturer P/N SN74LVC3G17DCTR

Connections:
+3V3: C93.2, C98.1, R92.2, U22.10 (VDDA), U22.48 (VDD), U23.8 (VCC); also elsewhere on the board
+5V: J28.5, R95.2, R96.2, R97.2; also elsewhere on the board
/DRIB_PROG: R82.1, U22.42 (BOOT0); also elsewhere on the board
/DRIB_UART_RX: U22.39 (PA15); also elsewhere on the board
/DRIB_UART_TX: U22.40 (PB6); also elsewhere on the board
/dribbler/H1: U22.11 (PA0), U23.7 (1Y)
/dribbler/H1_A: J28.3, R95.1, U23.1 (1A)
/dribbler/H2: U22.12 (PA1), U23.5 (2Y)
/dribbler/H2_A: J28.2, R96.1, U23.3 (2A)
/dribbler/H3: U22.13 (PA2), U23.2 (3Y)
/dribbler/H3_A: J28.1, R97.1, U23.6 (3A)
/dribbler/HSU: R83.1, U22.33 (HSU)
/dribbler/HSV: R85.1, U22.29 (HSV)
/dribbler/HSW: R87.1, U22.25 (HSW)
/dribbler/LSU: R84.1, U22.36 (LSU)
/dribbler/LSV: R86.1, U22.32 (LSV)
/dribbler/LSW: R88.1, U22.28 (LSW)
/dribbler/MOTOR_LED: Q35.1 (G), U22.19 (PB1)
/dribbler/PHASE_U: C95.2, J28.8, Q29.3 (S), Q30.2 (D), U22.34 (OUTU)
/dribbler/PHASE_V: C96.2, J28.7, Q31.3 (S), Q32.2 (D), U22.30 (OUTV)
/dribbler/PHASE_W: C97.2, J28.6, Q33.3 (S), Q34.2 (D), U22.26 (OUTW)
/dribbler/SENSE_N1: R91.2, R94.1, U22.22 (OP1N)
/dribbler/SENSE_O1: R94.2, U22.14 (PA3), U22.21 (OP1O), U22.24 (OC_COMP)
/dribbler/SENSE_P1: R90.2, R93.1, U22.23 (OP1P)
/dribbler/SWD_CLK: J29.2, U22.38 (PA14_SWD_CLK)
/dribbler/SWD_IO: J29.1, U22.37 (PA13_SWD_IO)
/~DRIB_RST: U22.7 (NRST); also elsewhere on the board
GND: C93.1, C94.2, C98.2, C99.2, C100.2, C101.2, C102.2, C103.2, C104.2, C105.2, C106.2, C107.2, C108.2, C109.2, J28.4, Q35.2 (S), R82.2, R89.1, R91.1, R93.2, U22.1 (OP2P), U22.20 (TESTMODE), U22.44 (GND), U22.45 (OP3P), U22.49 (EPAD), U23.4 (GND); also elsewhere on the board
unnamed: D8.2 (A), R92.1
unnamed: D8.1 (K), Q35.3 (D)
unnamed: Q29.1 (G), R83.2
unnamed: Q30.1 (G), R84.2
unnamed: Q30.3 (S), Q32.3 (S), Q34.3 (S), R89.2, R90.1
unnamed: Q31.1 (G), R85.2
unnamed: Q32.1 (G), R86.2
unnamed: Q33.1 (G), R87.2
unnamed: Q34.1 (G), R88.2
unnamed: U22.2 (OP2N), U22.3 (OP2O)
unnamed: U22.46 (OP3N), U22.47 (OP3O)
unnamed: C95.1, U22.35 (VBOOTU)
unnamed: C96.1, U22.31 (VBOOTV)
unnamed: C97.1, U22.27 (VBOOTW)
unnamed: C94.1, U22.6 (VREG12)
VDC: C99.1, C100.1, C101.1, C102.1, C103.1, C104.1, C105.1, C106.1, C107.1, C108.1, C109.1, Q29.2 (D), Q31.2 (D), Q33.2 (D), U22.8 (VM); also elsewhere on the board

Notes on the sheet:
Dribbler motor: Maxon EC 16, brushless, 30 Watt
Low Side BLDC Current Sensing
TODO: Change this connector
Config for unused op amps
Wrong connector for the dribbler motor we have
SWD Header
DRIBBLER status LED
Want: Molex 0353630860
Two decoupling for each phase line
Motor and Hall Sensor Connectors
4 VDC general decoupling
large decoupling
Schmitt triggers. Analog to digital conversion using positive feedback.
UART_TX moved from PA14 to PB6
N.G. Pin order is flipped from what's listed on Maxon datasheet. Just look at the colors.
